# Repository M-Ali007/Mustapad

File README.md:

# Mustapad

### Inspiration
I thought that this could be a great additon to my setup and I could learn a lot from doing this so I made this. It was hard but I learnt a bunch.

### Challenges
This was pretty hard - I've never done anything like this ever - but it all paid off and I have a super cool design now

### A screenshot of my overall hackpad

### A screenshot of my schematic

### A screenshot of My PCB

### A screenshot of My case and how it'll fit together

### a BOM for my parts
- 1x Seeed XIAO RP2040
- 6x MX-Style switches
- 6x Blank DSA keycaps (White)
- 2x SK6812 MINI-E LEDs
- 4x M3x16mm screws
- 6x M3x5mx4mm heatset inserts

I learnt a bunch from this project it was super fun :D

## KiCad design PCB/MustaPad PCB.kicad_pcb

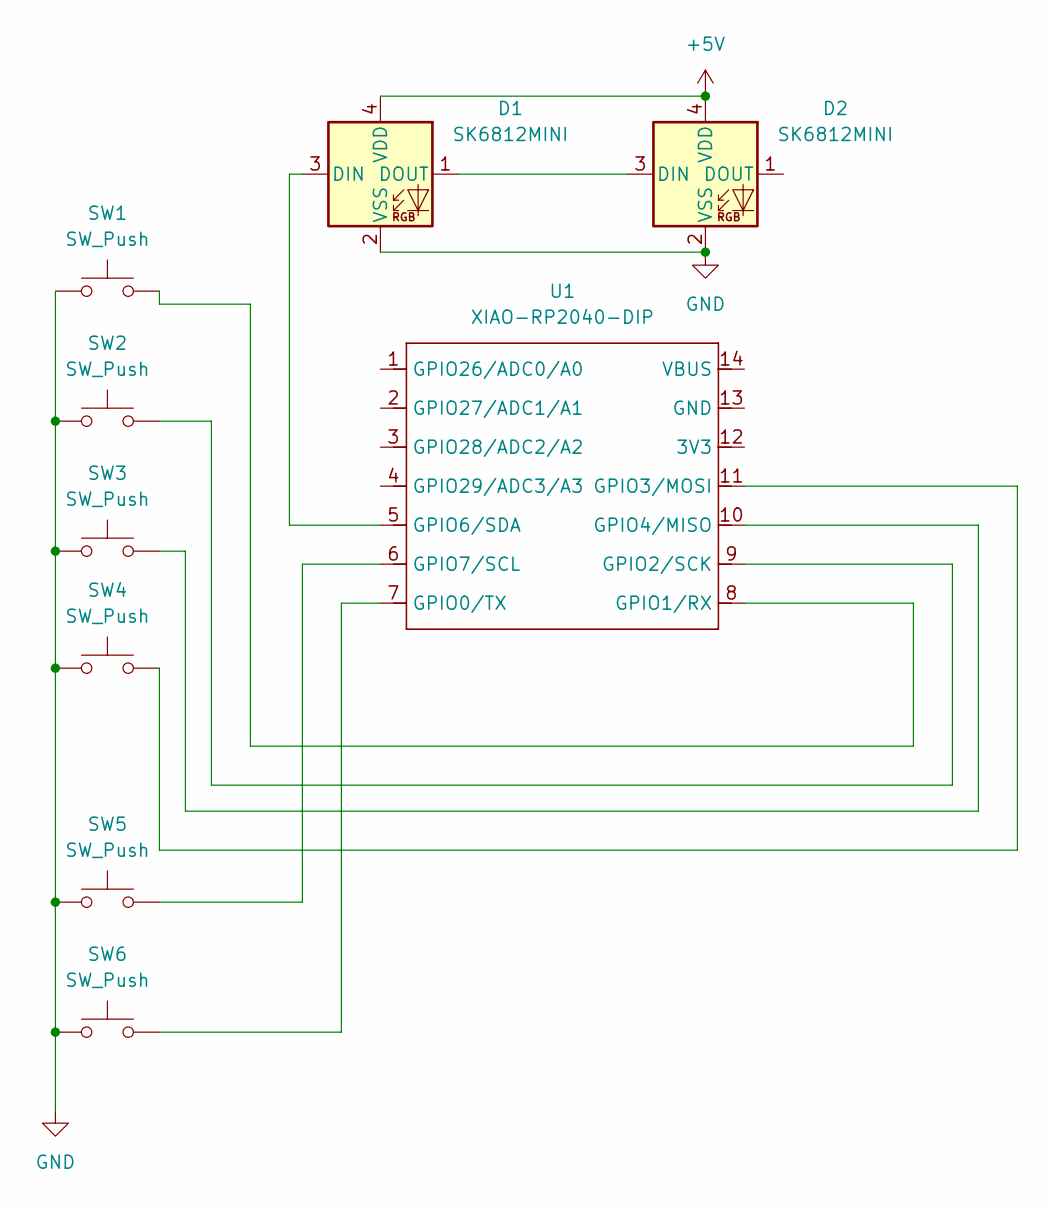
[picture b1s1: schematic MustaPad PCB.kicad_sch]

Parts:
D1, D2: SK6812MINI; LED_SK6812MINI_PLCC4_3.5x3.5mm_P1.75mm
SW1, SW2, SW3, SW4, SW5, SW6: SW_Push; SW_Cherry_MX_1.00u_PCB
U1: XIAO-RP2040-DIP

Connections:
+5V: D1.4 (VDD), D2.4 (VDD)
GND: D1.2 (VSS), D2.2 (VSS), SW1.1, SW2.1, SW3.1, SW4.1, SW5.1, SW6.1
unnamed: D1.3 (DIN), U1.5 (GPIO6/SDA)
unnamed: D1.1 (DOUT), D2.3 (DIN)
unnamed: SW6.2, U1.7 (GPIO0/TX)
unnamed: SW1.2, U1.8 (GPIO1/RX)
unnamed: SW2.2, U1.9 (GPIO2/SCK)
unnamed: SW4.2, U1.11 (GPIO3/MOSI)
unnamed: SW3.2, U1.10 (GPIO4/MISO)
unnamed: SW5.2, U1.6 (GPIO7/SCL)

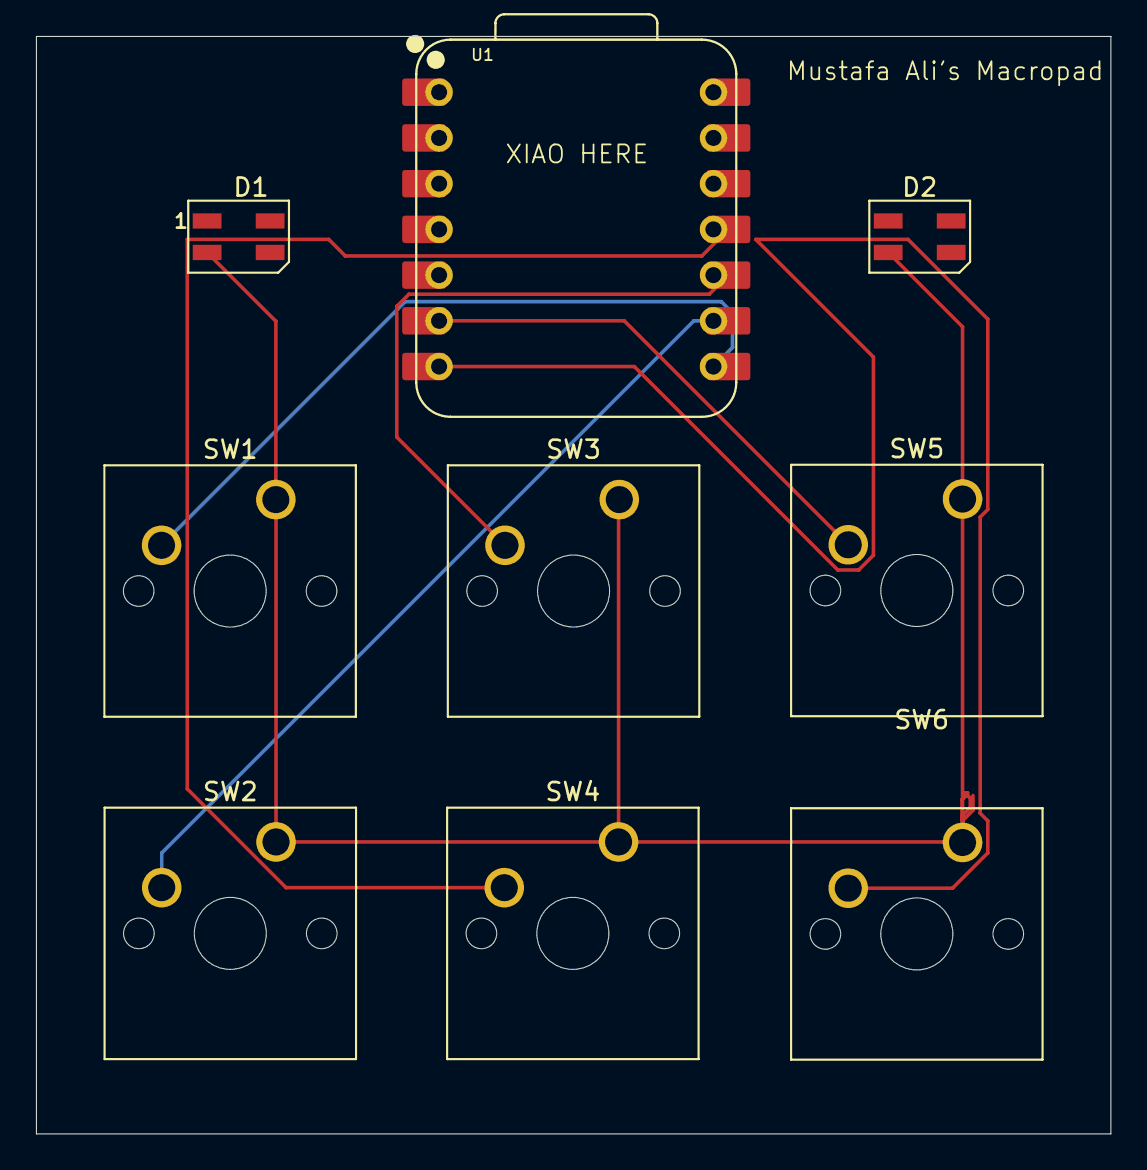
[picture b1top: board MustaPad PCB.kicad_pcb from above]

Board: 2 copper layers, 59.7 x 61.0 mm, 9 parts (0 on the bottom side), 10 nets.

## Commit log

2025-12-04 Added Files
2025-12-04 added firmware
2025-12-04 Created firmware folder
2025-12-04 Created PCB
2025-12-04 Added CAD
2025-12-04 Rename MustaPad PCB.kicad_pro to PCB/MustaPad PCB.kicad_pro
2025-12-04 added pin numbers
2025-12-04 Enhance README with additional details and images
    Added sections for inspiration, screenshots, and BOM in README.
2025-12-04 Update case screenshot section title in README
2025-12-04 Add personal reflection to README
    Added personal reflection on the project experience.
2025-12-04 Fix typo in README.md
2025-12-04 updated assembled .step model
2025-12-04 Create asdf
2025-12-04 Rename MustaPad Fully Assembled.step to CAD/MustaPad Fully Assembled.step
